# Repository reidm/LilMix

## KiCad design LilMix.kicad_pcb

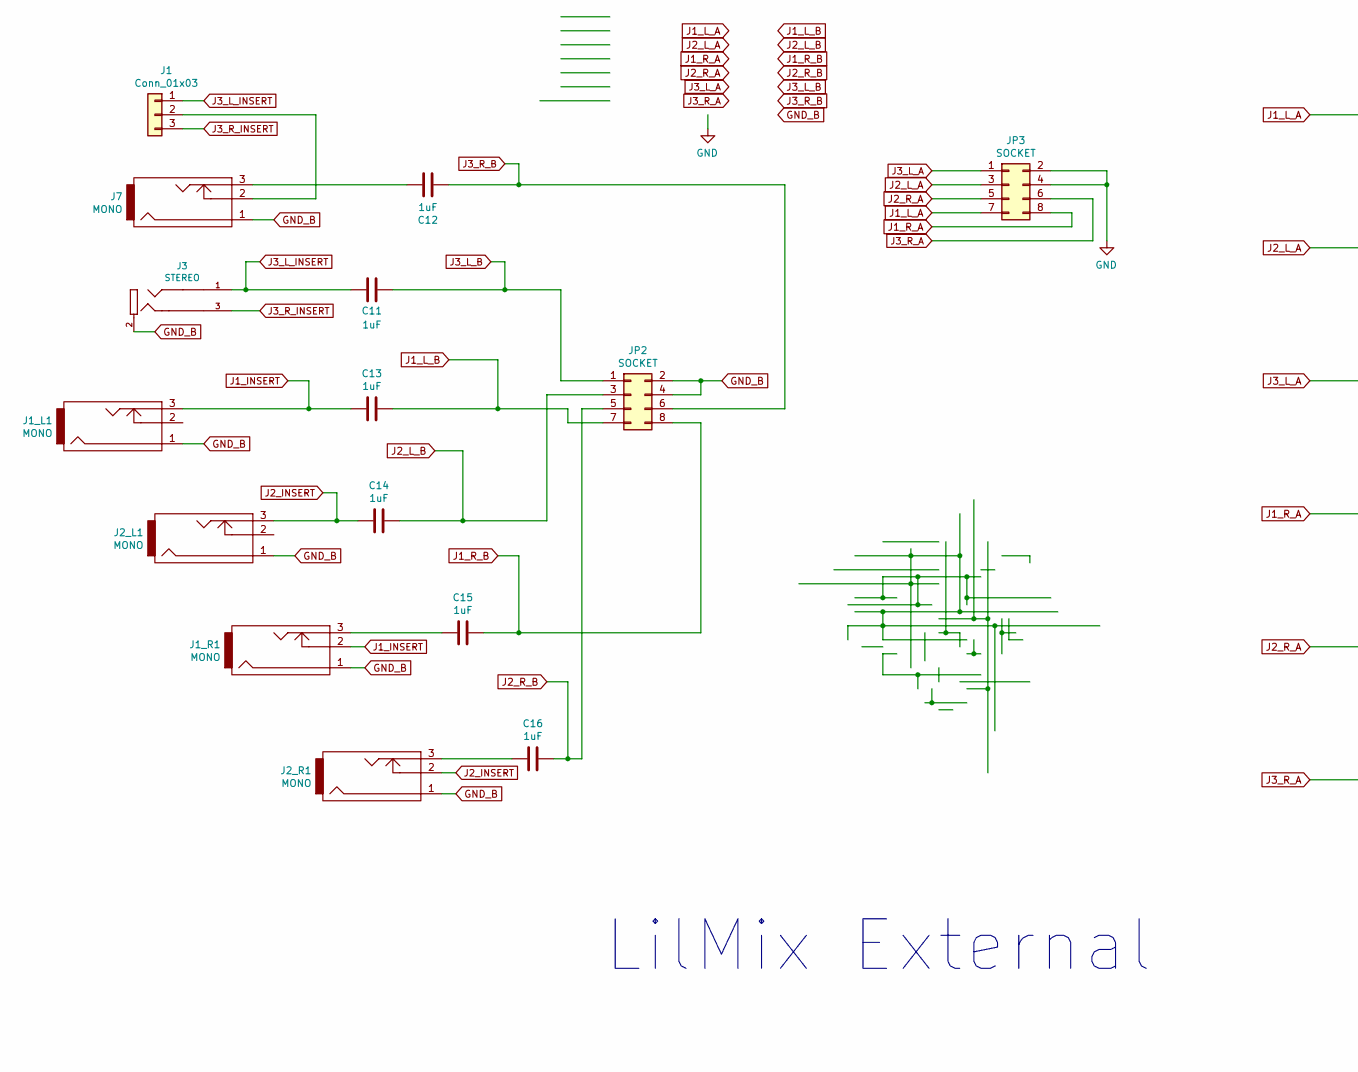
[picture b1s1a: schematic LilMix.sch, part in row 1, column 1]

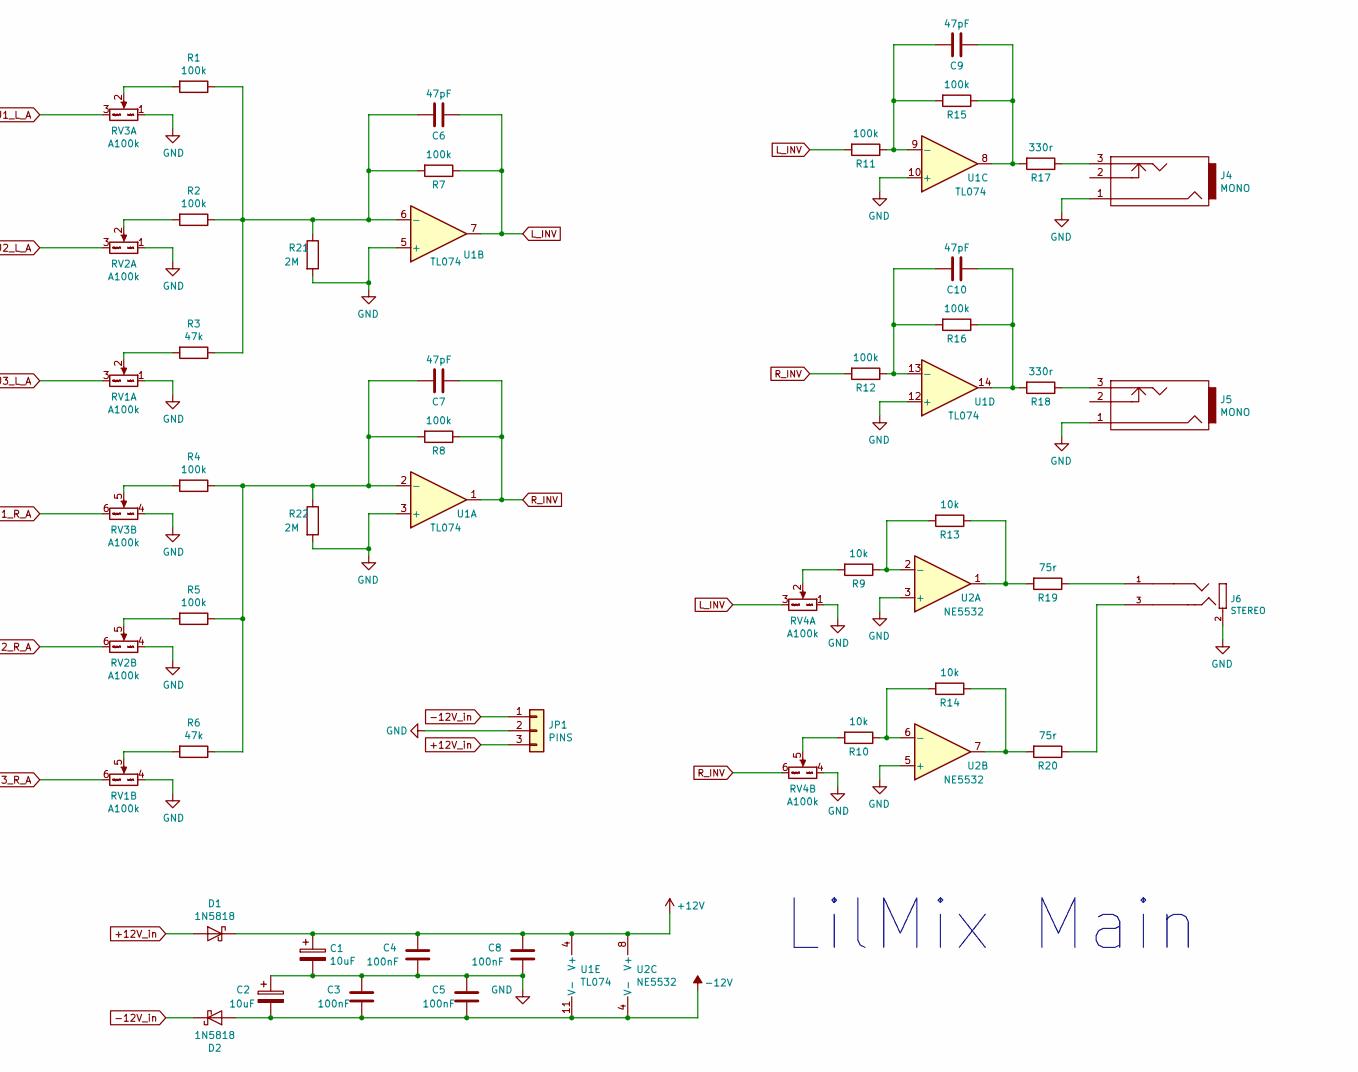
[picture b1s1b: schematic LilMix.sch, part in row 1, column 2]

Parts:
C1, C2: 10uF; C_0805_2012Metric_Pad1.15x1.40mm_HandSolder
C3, C4, C5, C8: 100nF; C_0805_2012Metric_Pad1.15x1.40mm_HandSolder
C6, C7, C9, C10: 47pF; C_0805_2012Metric_Pad1.15x1.40mm_HandSolder
C11, C12, C13, C14, C15, C16: 1uF; C_Rect_L7.0mm_W4.5mm_P5.00mm
D1, D2: 1N5818; D_SOD-123
J1: Conn_01x03; PinHeader_1x03_P2.54mm_Vertical
J1_L1, J1_R1, J2_L1, J2_R1, J7: MONO; PJ301M-12-CC-TIGHT
J3, J6: STEREO; STPX-3501-3C-1
J4, J5: MONO; EighthInch_PJ301BM_CC_FIXED
JP1: PINS; PinSocket_1x03_P2.54mm_Vertical
JP2, JP3: SOCKET; Socket_2x4_2.54mm_TH
R1, R2, R4, R5, R7, R8, R11, R12, R15, R16: 100k; R_0805_2012Metric_Pad1.15x1.40mm_HandSolder
R3, R6: 47k; R_0805_2012Metric_Pad1.15x1.40mm_HandSolder
R9, R10, R13, R14: 10k; R_0805_2012Metric_Pad1.15x1.40mm_HandSolder
R17, R18: 330r; R_0805_2012Metric_Pad1.15x1.40mm_HandSolder
R19, R20: 75r; R_0805_2012Metric_Pad1.15x1.40mm_HandSolder
R21, R22: 2M; R_0805_2012Metric_Pad1.15x1.40mm_HandSolder
RV1, RV2, RV3, RV4: A100k; Potentiometer_Alpha_RD902F-40-00D_Dual_Vertical
U1: TL074; SOIC-14_3.9x8.7mm_P1.27mm
U2: NE5532; SOIC-8_3.9x4.9mm_P1.27mm

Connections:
+12V: C1.1, C4.1, C8.1, D1.1 (K), U1.4 (V+), U2.8 (V+)
+12V_in: D1.2 (A), JP1.3
-12V: C2.2, C3.2, C5.2, D2.2 (A), U1.11 (V-), U2.4 (V-)
-12V_in: D2.1 (K), JP1.1
GND: C1.2, C2.1, C3.1, C4.2, C5.1, C8.2, J4.1, J5.1, J6.2 (SLEEVE), JP1.2, JP3.2, JP3.4, R21.2, R22.2, RV1.1 (Left), RV1.4 (Left), RV2.1 (Left), RV2.4 (Left), RV3.1 (Left), RV3.4 (Left), RV4.1 (Left), RV4.4 (Left), U1.3 (+), U1.5 (+), U1.10 (+), U1.12 (+), U2.3 (+), U2.5 (+)
GND_B: J1_L1.1, J1_R1.1, J2_L1.1, J2_R1.1, J3.2 (SLEEVE), J7.1, JP2.2, JP2.4
J1_INSERT: C13.2, J1_L1.3, J1_R1.2
J1_L_A: JP3.7, RV3.3 (Right)
J1_L_B: C13.1, JP2.7
J1_R_A: JP3.8, RV3.6 (Right)
J1_R_B: C15.1, JP2.8
J2_INSERT: C14.2, J2_L1.3, J2_R1.2
J2_L_A: JP3.3, RV2.3 (Right)
J2_L_B: C14.1, JP2.3
J2_R_A: JP3.5, RV2.6 (Right)
J2_R_B: C16.1, JP2.5
J3_L_A: JP3.1, RV1.3 (Right)
J3_L_B: C11.1, JP2.1
J3_L_INSERT: C11.2, J1.1, J3.1 (TIP)
J3_R_A: JP3.6, RV1.6 (Right)
J3_R_B: C12.2, JP2.6
J3_R_INSERT: J1.3, J3.3 (TIP-SW)
L_INV: C6.1, R7.1, R11.2, RV4.3 (Right), U1.7
unnamed: C6.2, R1.1, R2.1, R3.1, R7.2, R21.1, U1.6 (-)
unnamed: C7.2, R4.1, R5.1, R6.1, R8.2, R22.1, U1.2 (-)
unnamed: C9.1, R15.1, R17.2, U1.8
unnamed: C9.2, R11.1, R15.2, U1.9 (-)
unnamed: C10.1, R16.1, R18.2, U1.14
unnamed: C10.2, R12.1, R16.2, U1.13 (-)
unnamed: C12.1, J7.3
unnamed: C15.2, J1_R1.3
unnamed: C16.2, J2_R1.3
unnamed: J1.2, J7.2
unnamed: J4.3, R17.1
unnamed: J5.3, R18.1
unnamed: J6.1 (TIP), R19.1
unnamed: J6.3 (TIP-SW), R20.1
unnamed: R1.2, RV3.2 (Center)
unnamed: R2.2, RV2.2 (Center)
unnamed: R3.2, RV1.2 (Center)
unnamed: R4.2, RV3.5 (Center)
unnamed: R5.2, RV2.5 (Center)
unnamed: R6.2, RV1.5 (Center)
unnamed: R9.2, RV4.2 (Center)
unnamed: R10.1, R14.2, U2.6 (-)
unnamed: R10.2, RV4.5 (Center)
unnamed: R13.1, R19.2, U2.1
unnamed: R9.1, R13.2, U2.2 (-)
unnamed: R14.1, R20.2, U2.7
R_INV: C7.1, R8.1, R12.2, RV4.6 (Right), U1.1

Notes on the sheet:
LilMix Main
LilMix External

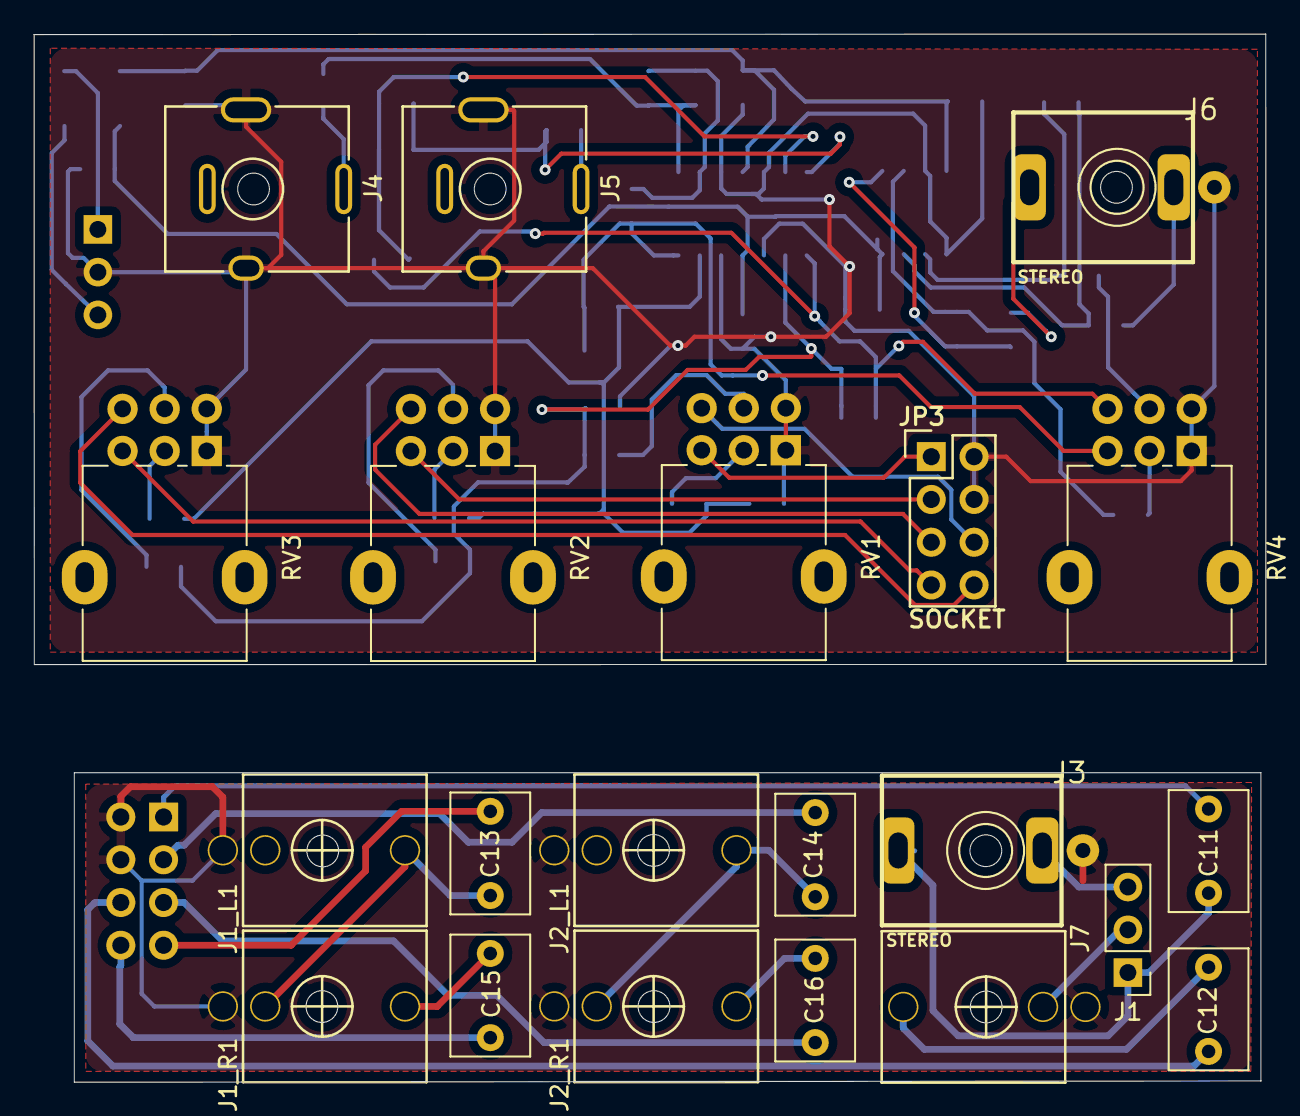
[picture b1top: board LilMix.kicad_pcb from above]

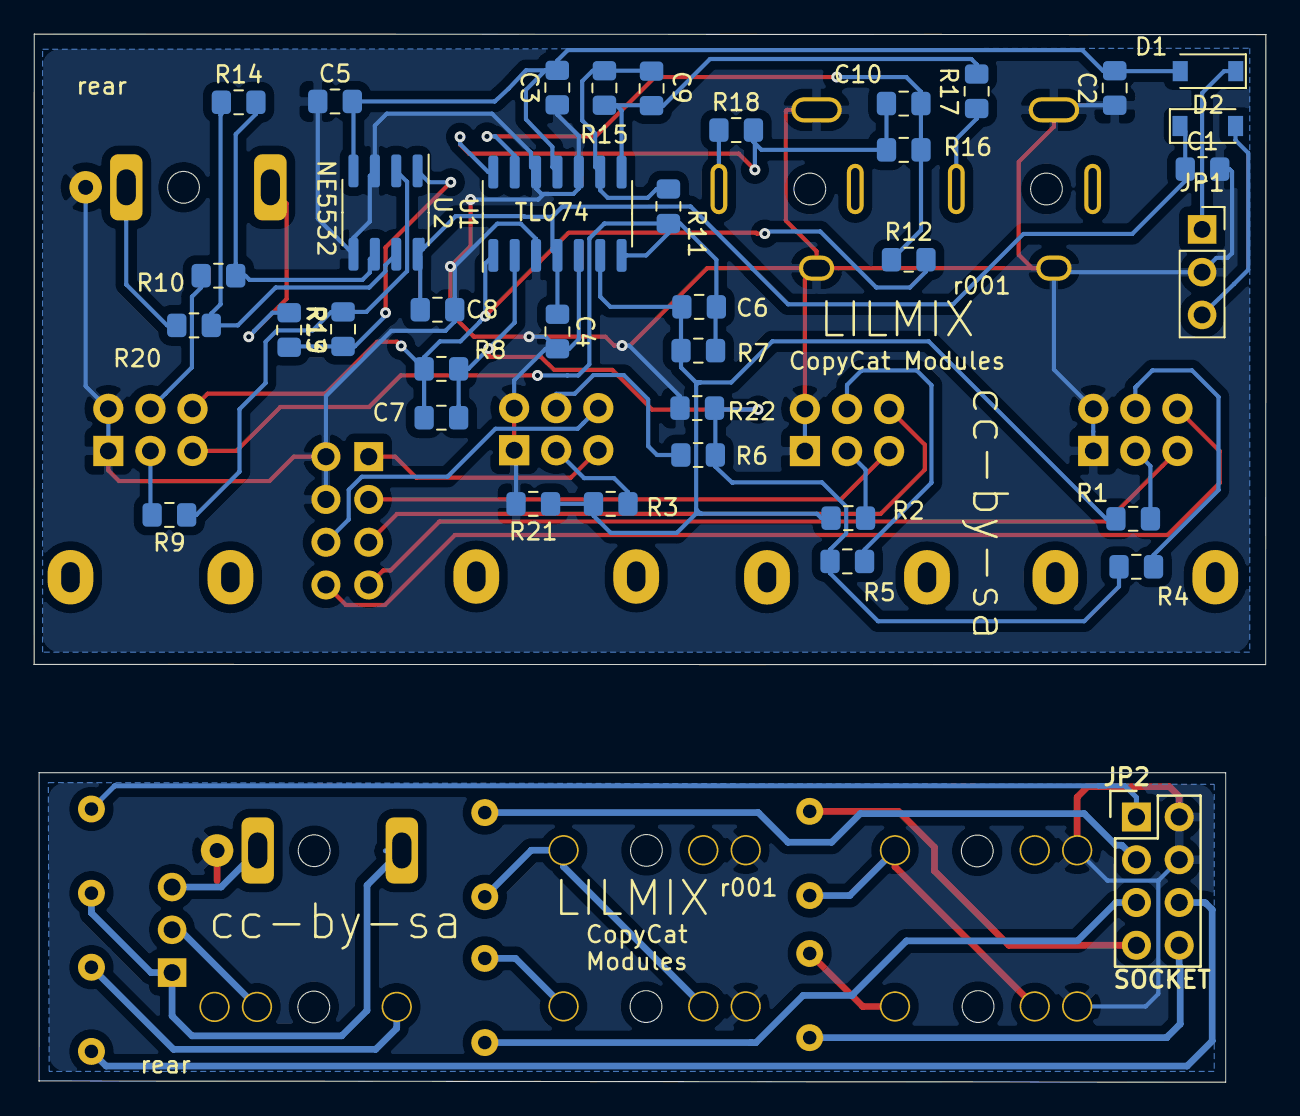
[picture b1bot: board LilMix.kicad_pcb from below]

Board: 2 copper layers, 73.2 x 62.3 mm, 59 parts (38 on the bottom side), 50 nets.

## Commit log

2020-02-11 Initial version of circuit
2020-02-11 Updated to stereo jacks, replaced IC caps
2020-02-11 Very rough component placement
2020-02-15 Updated rough placement and circuit updates
2020-02-15 Rought placement complete
2020-02-15 Updated project traces. Added board cuts
2020-02-15 Added power sockets for other modules
2020-02-15 Updated footprint of stereo jacks
2020-02-15 Added dc filtering capacitors to inputs
2020-02-15 Nearly complete routings
2020-02-15 Added another +12v socket header. Initial routing completed
2020-02-15 Removed extra tracks and vias. Increased trace sizes around the board
2020-02-15 Flipped power headers
2020-02-20 Fixed jack destinatios and flipped front board orientation. Rerouted pcb
2020-02-20 Components moved, board wiring needs to be redone. Removed trim pots on line out. Replaced jacks on large board
2020-02-21 Finished initial routing
2020-02-21 Removed extra jack connection from schematic. Added second jack to 3rd channel. Repositioned jack board for even space between jacks, with slightly reduced overall dimensions
2020-02-21 Fixed J7 insert
2020-02-22 Change TL074 output channel feedback resistors, based on BB results
2020-02-22 Fix J1 insert from T rather than S
2020-02-26 Add header pins to chose normal options on channel 3
2020-03-18 Moved jack in line with it's neighbours
2020-03-25 Reduced top board width.
2020-04-08 Change diode values
2020-04-10 Footprints changed and title text added
2020-04-10 r001 gerber set
2020-04-11 Zipped gerbers
2020-06-09 Fixed fp on mono jacks.
2020-06-13 r001.1 gerber
2020-06-21 Final gerbers
2020-06-21 gerbers_b/LilMix-B-r001.zip
2020-06-21 Removed old file.
2020-06-21 fp cache update

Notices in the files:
LilMix.kicad_pcb:
cc-by-sa
